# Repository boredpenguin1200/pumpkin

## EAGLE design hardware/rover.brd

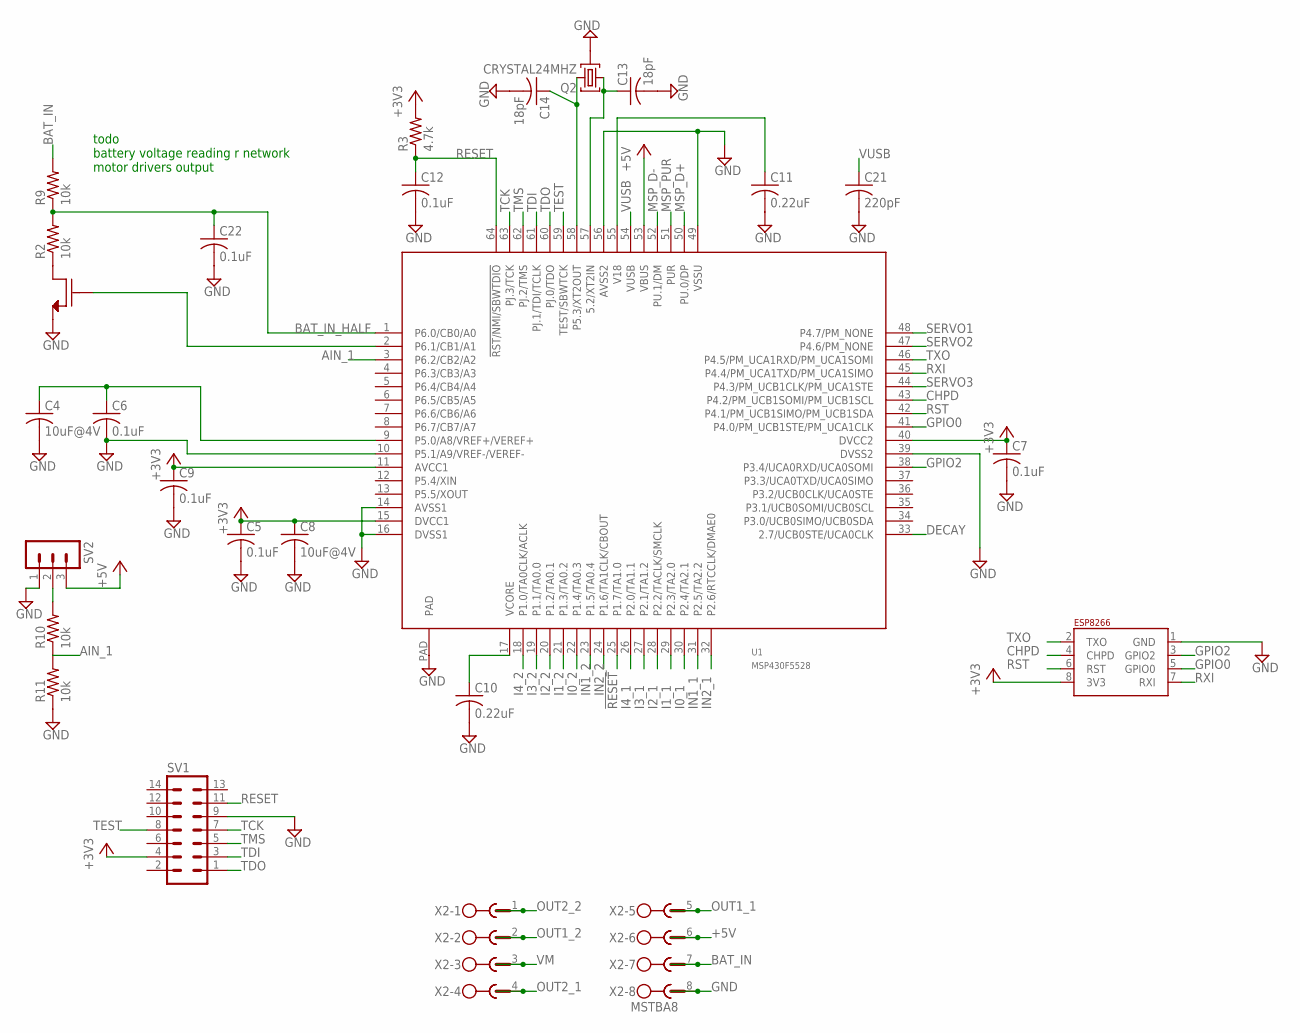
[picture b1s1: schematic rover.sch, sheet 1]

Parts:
C4, C8: 10uF@4V; C0603
C5, C6, C7, C9, C12, C22: 0.1uF; C0603
C10, C11: 0.22uF; C0603
C13, C14: 18pF; C0603
C21: 220pF; C0603
Q2: CRYSTAL24MHZ; ABM8
R2, R9, R10, R11: 10k; R0603
R3: 4.7k; R0603
SV1: MA07-2THM; MA07-2
SV2: MA03-1RND; MA03-1-ROUND
U1: MSP430F5528; -RGC-N64
U3: NMOS2N7002P; 2N7002P-235
U15: ESP8266
X2: MSTBA8

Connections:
!RESET: U1.25 (P1.7/TA1.0); also elsewhere on the board
+3V3: C5.1, C7.1, C8.1, C9.1, R3.2, SV1.4, U1.11 (AVCC1), U1.15 (DVCC1), U1.40 (DVCC2), U15.8 (3V3); also elsewhere on the board
+5V: SV2.3, U1.53 (VBUS), X2.6; also elsewhere on the board
AIN_1: R10.1, R11.2, U1.3 (P6.2/CB2/A2)
BAT_IN: R9.2, X2.7
BAT_IN_HALF: C22.1, R2.2, R9.1, U1.1 (P6.0/CB0/A0)
CHPD: U1.43 (P4.2/PM_UCB1SOMI/PM_UCB1SCL), U15.4 (CHPD)
DECAY: U1.33 (2.7/UCB0STE/UCA0CLK); also elsewhere on the board
GND: C4.2, C5.2, C6.2, C7.2, C8.2, C9.2, C10.2, C11.2, C12.2, C13.2, C14.2, C21.2, C22.2, Q2.2, Q2.4 (2), R11.1, SV1.9, SV2.1, U1.10 (P5.1/A9/VREF-/VEREF-), U1.14 (AVSS1), U1.16 (DVSS1), U1.39 (DVSS2), U1.49 (VSSU), U1.56 (AVSS2), U1.PAD, U3.3 (D), U15.1 (GND), X2.8; also elsewhere on the board
GPIO0: U1.41 (P4.0/PM_UCB1STE/PM_UCA1CLK), U15.5 (GPIO0)
GPIO2: U1.38 (P3.4/UCA0RXD/UCA0SOMI), U15.3 (GPIO2)
I0_1: U1.30 (P2.4/TA2.1); also elsewhere on the board
I0_2: U1.22 (P1.4/TA0.3); also elsewhere on the board
I1_1: U1.29 (P2.3/TA2.0); also elsewhere on the board
I1_2: U1.21 (P1.3/TA0.2); also elsewhere on the board
I2_1: U1.28 (P2.2/TACLK/SMCLK); also elsewhere on the board
I2_2: U1.20 (P1.2/TA0.1); also elsewhere on the board
I3_1: U1.27 (P2.1/TA1.2); also elsewhere on the board
I3_2: U1.19 (P1.1/TA0.0); also elsewhere on the board
I4_1: U1.26 (P2.0/TA1.1); also elsewhere on the board
I4_2: U1.18 (P1.0/TA0CLK/ACLK); also elsewhere on the board
IN1_1: U1.31 (P2.5/TA2.2); also elsewhere on the board
IN1_2: U1.23 (P1.5/TA0.4); also elsewhere on the board
IN2_1: U1.32 (P2.6/RTCCLK/DMAE0); also elsewhere on the board
IN2_2: U1.24 (P1.6/TA1CLK/CBOUT); also elsewhere on the board
MSP_D+: U1.50 (PU.0/DP); also elsewhere on the board
MSP_D-: U1.52 (PU.1/DM); also elsewhere on the board
MSP_PUR: U1.51 (PUR); also elsewhere on the board
unnamed: R2.1, U3.2 (S)
unnamed: C11.1, U1.55 (V18)
unnamed: C10.1, U1.17 (VCORE)
unnamed: U1.2 (P6.1/CB1/A1), U3.1 (G)
unnamed: C13.1, Q2.1, U1.57 (5.2/XT2IN)
unnamed: C14.1, Q2.3, U1.58 (P5.3/XT2OUT)
unnamed: R10.2, SV2.2
unnamed: C4.1, C6.1, U1.9 (P5.0/A8/VREF+/VEREF+)
OUT1_1: X2.5; also elsewhere on the board
OUT1_2: X2.2; also elsewhere on the board
OUT2_1: X2.4; also elsewhere on the board
OUT2_2: X2.1; also elsewhere on the board
RESET: C12.1, R3.1, SV1.11, U1.64 (!RST/NMI/SBWTDIO)
RST: U1.42 (P4.1/PM_UCB1SIMO/PM_UCB1SDA), U15.6 (RST)
RXI: U1.45 (P4.4/PM_UCA1TXD/PM_UCA1SIMO), U15.7 (RXI)
SERVO1: U1.48 (P4.7/PM_NONE); also elsewhere on the board
SERVO2: U1.47 (P4.6/PM_NONE); also elsewhere on the board
SERVO3: U1.44 (P4.3/PM_UCB1CLK/PM_UCA1STE); also elsewhere on the board
TCK: SV1.7, U1.63 (PJ.3/TCK)
TDI: SV1.3, U1.61 (PJ.1/TDI/TCLK)
TDO: SV1.1, U1.60 (PJ.0/TDO)
TEST: SV1.8, U1.59 (TEST/SBWTCK)
TMS: SV1.5, U1.62 (PJ.2/TMS)
TXO: U1.46 (P4.5/PM_UCA1RXD/PM_UCA1SOMI), U15.2 (TXO)
VM: X2.3; also elsewhere on the board
VUSB: C21.1, U1.54 (VUSB)

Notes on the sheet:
todo battery voltage reading r network motor drivers output

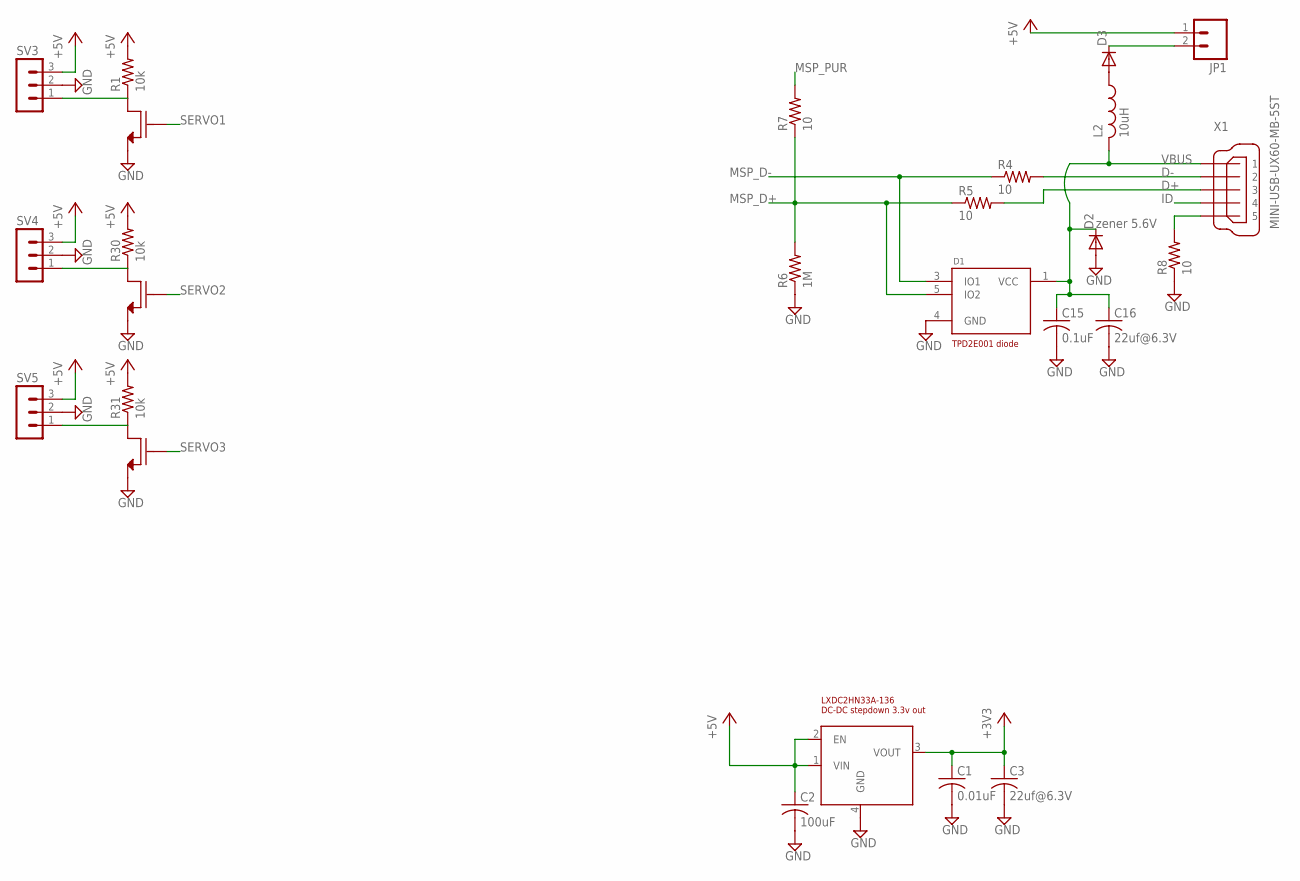
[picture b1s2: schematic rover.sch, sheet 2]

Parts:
C1: 0.01uF; C0603
C2: 100uF; 875105344010
C3, C16: 22uf@6.3V; C0603
C15: 0.1uF; C0603
D1: USB-DIODE; -DRL
D2: zener 5.6V; SOD123
D3: DIODE-; DB2X20700L
JP1: M02PTH; 1X02
L2: 10uH; VLS201610ET
R1, R30, R31: 10k; R0603
R4, R5, R7, R8: 10; R0603
R6: 1M; R0603
SV3, SV4, SV5: MA03-1RND; MA03-1-ROUND
U2: LXDC2HN33A-136
U8, U9, U10: NMOS2N7002P; 2N7002P-235
X1: MINI-USB-UX60-MB-5ST; UX60-MB-5ST

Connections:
+3V3: C1.1, C3.1, U2.3 (VOUT); also elsewhere on the board
+5V: C2.P$1 (1), JP1.1, R1.2, R30.2, R31.2, SV3.3, SV4.3, SV5.3, U2.1 (VIN), U2.2 (EN); also elsewhere on the board
D+: R5.2, X1.3
D-: R4.2, X1.2
GND: C1.2, C2.P$2 (2), C3.2, C15.2, C16.2, D1.4 (GND), D2.A, R6.1, R8.1, SV3.2, SV4.2, SV5.2, U2.4 (GND), U8.3 (D), U9.3 (D), U10.3 (D); also elsewhere on the board
ID: X1.4
MSP_D+: D1.5 (IO2), R5.1, R6.2, R7.1; also elsewhere on the board
MSP_D-: D1.3 (IO1), R4.1; also elsewhere on the board
MSP_PUR: R7.2; also elsewhere on the board
unnamed: R8.2, X1.5
unnamed: D3.P$1 (A), L2.P$1 (1)
unnamed: D3.P$2 (C), JP1.2
unnamed: R1.1, SV3.1, U8.2 (S)
unnamed: R30.1, SV4.1, U9.2 (S)
unnamed: R31.1, SV5.1, U10.2 (S)
SERVO1: U8.1 (G); also elsewhere on the board
SERVO2: U9.1 (G); also elsewhere on the board
SERVO3: U10.1 (G); also elsewhere on the board
VBUS: C15.1, C16.1, D1.1 (VCC), D2.C, L2.P$2 (2), X1.1

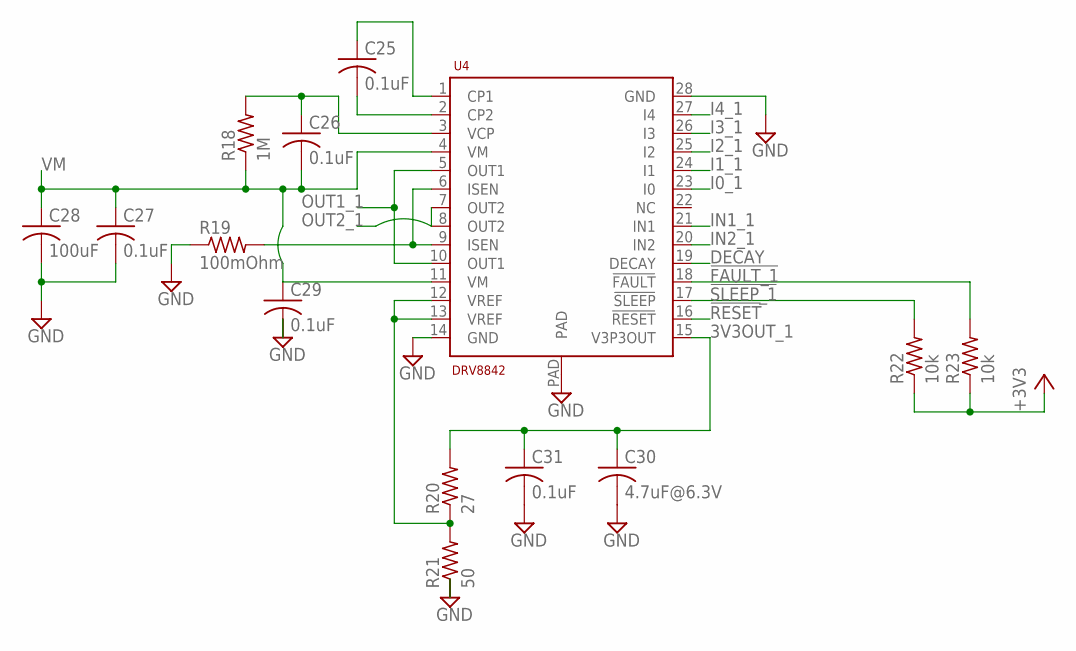
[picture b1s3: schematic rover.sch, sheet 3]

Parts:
C25, C26, C27, C29, C31: 0.1uF; C0603
C28: 100uF; 875105344010
C30: 4.7uF@6.3V; C0603
R18: 1M; R0603
R19: 100mOhm; R0603
R20: 27; R0603
R21: 50; R0603
R22, R23: 10k; R0603
U4: DRV8842; -PWP

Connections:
3V3OUT_1: C30.1, C31.1, R20.2, U4.15 (V3P3OUT)
!FAULT_1: R23.2, U4.18 (!FAULT)
!RESET: U4.16 (!RESET); also elsewhere on the board
!SLEEP_1: R22.2, U4.17 (!SLEEP)
+3V3: R22.1, R23.1; also elsewhere on the board
CP1: C25.2, U4.2 (CP2)
CP2: C25.1, U4.1 (CP1)
DECAY: U4.19 (DECAY); also elsewhere on the board
GND: C27.2, C28.P$2 (2), C29.2, C30.2, C31.2, R19.1, R21.1, U4.14 (GND), U4.28 (GND), U4.PAD; also elsewhere on the board
I0_1: U4.23 (I0); also elsewhere on the board
I1_1: U4.24 (I1); also elsewhere on the board
I2_1: U4.25 (I2); also elsewhere on the board
I3_1: U4.26 (I3); also elsewhere on the board
I4_1: U4.27 (I4); also elsewhere on the board
IN1_1: U4.21 (IN1); also elsewhere on the board
IN2_1: U4.20 (IN2); also elsewhere on the board
ISEN: R19.2, U4.6 (ISEN), U4.9 (ISEN)
OUT1_1: U4.5 (OUT1), U4.10 (OUT1); also elsewhere on the board
OUT2_1: U4.7 (OUT2), U4.8 (OUT2); also elsewhere on the board
VCP: C26.1, R18.2, U4.3 (VCP)
VM: C26.2, C27.1, C28.P$1 (1), C29.1, R18.1, U4.4 (VM), U4.11 (VM); also elsewhere on the board
VREF: R20.1, R21.2, U4.12 (VREF), U4.13 (VREF)

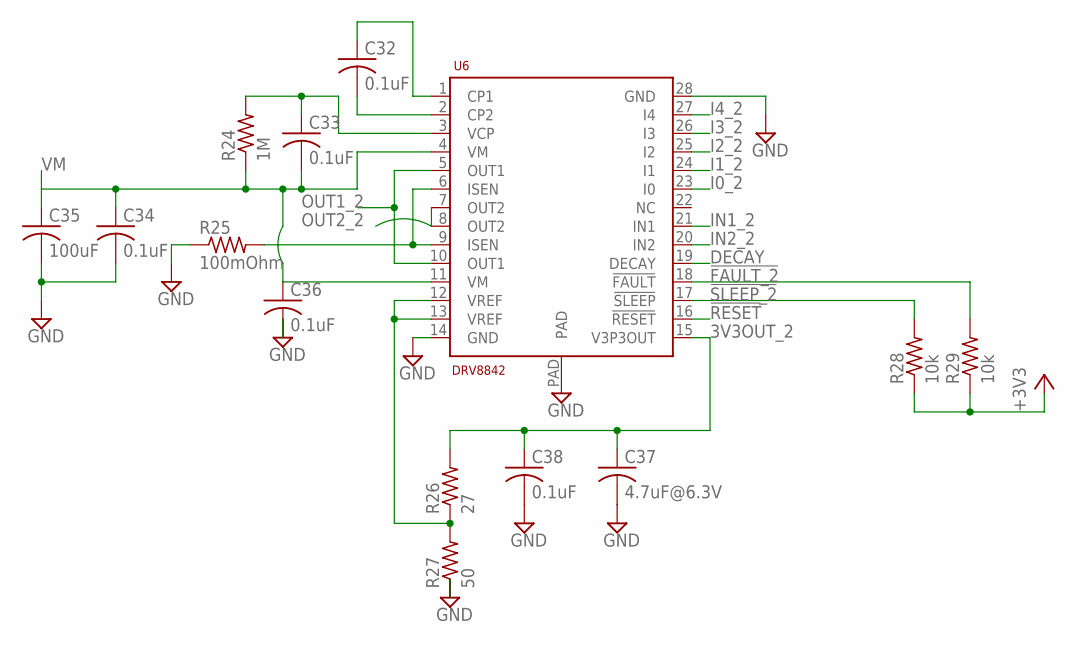
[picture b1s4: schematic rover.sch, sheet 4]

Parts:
C32, C33, C34, C36, C38: 0.1uF; C0603
C35: 100uF; 875105344010
C37: 4.7uF@6.3V; C0603
R24: 1M; R0603
R25: 100mOhm; R0603
R26: 27; R0603
R27: 50; R0603
R28, R29: 10k; R0603
U6: DRV8842; -PWP

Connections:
3V3OUT_2: C37.1, C38.1, R26.2, U6.15 (V3P3OUT)
!FAULT_2: R29.2, U6.18 (!FAULT)
!RESET: U6.16 (!RESET); also elsewhere on the board
!SLEEP_2: R28.2, U6.17 (!SLEEP)
+3V3: R28.1, R29.1; also elsewhere on the board
CP3: C32.2, U6.2 (CP2)
CP4: C32.1, U6.1 (CP1)
DECAY: U6.19 (DECAY); also elsewhere on the board
GND: C34.2, C35.P$2 (2), C36.2, C37.2, C38.2, R25.1, R27.1, U6.14 (GND), U6.28 (GND), U6.PAD; also elsewhere on the board
I0_2: U6.23 (I0); also elsewhere on the board
I1_2: U6.24 (I1); also elsewhere on the board
I2_2: U6.25 (I2); also elsewhere on the board
I3_2: U6.26 (I3); also elsewhere on the board
I4_2: U6.27 (I4); also elsewhere on the board
IN1_2: U6.21 (IN1); also elsewhere on the board
IN2_2: U6.20 (IN2); also elsewhere on the board
ISEN1: R25.2, U6.6 (ISEN), U6.9 (ISEN)
OUT1_2: U6.5 (OUT1), U6.10 (OUT1); also elsewhere on the board
OUT2_2: U6.7 (OUT2), U6.8 (OUT2); also elsewhere on the board
VCP1: C33.1, R24.2, U6.3 (VCP)
VM: C33.2, C34.1, C35.P$1 (1), C36.1, R24.1, U6.4 (VM), U6.11 (VM); also elsewhere on the board
VREF1: R26.1, R27.2, U6.12 (VREF), U6.13 (VREF)

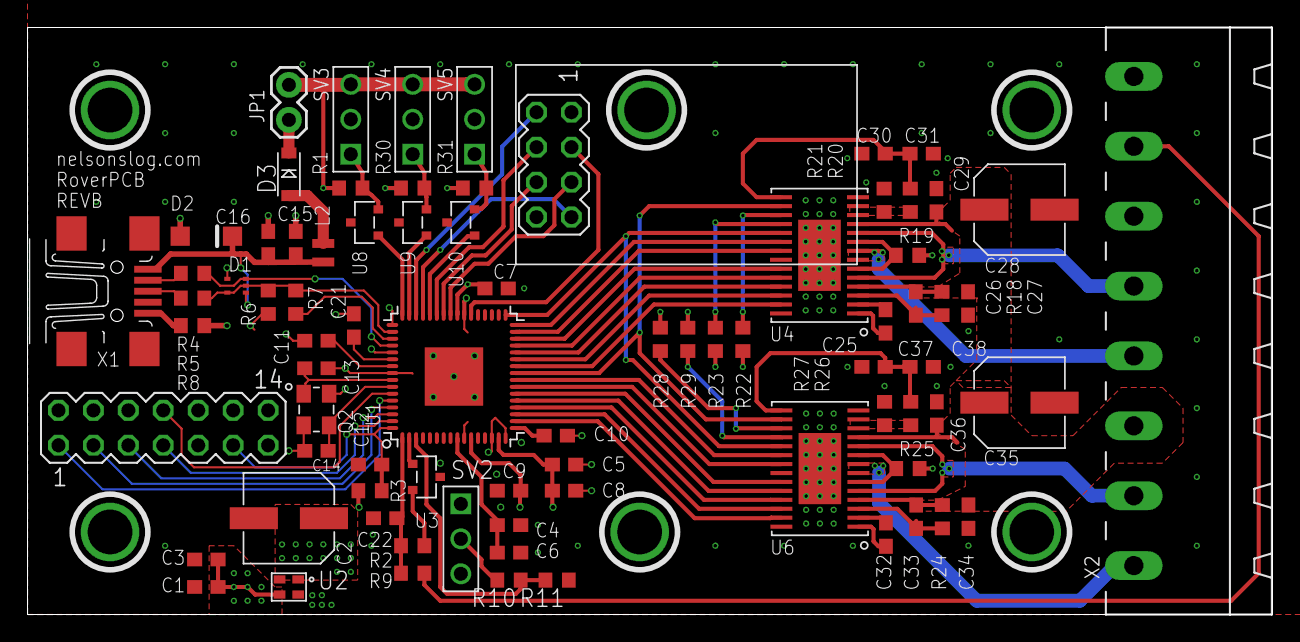
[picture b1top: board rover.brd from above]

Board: 4 copper layers, 90.5 x 42.7 mm, 79 parts (0 on the bottom side), 79 nets.

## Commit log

2016-12-27 init firmware
2016-12-27 fixed coms bug

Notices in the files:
parts and their libraries:
SparkFun-Connectors: Licensing: CC v3.0 Share-Alike You are welcome to use this library for commercial purposes.
